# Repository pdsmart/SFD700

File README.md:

# SFD-700

Repository updated 08/11/2023

v1.0 - Functions in most machines, albeit, for an MZ-700 it requires MZ-700 memory mapping logic if used outside of an MZ-1U06 expansion box. Recommend only to view, not to build.

v1.1 - Functions but restrictions imposed with the GAL registers (ie. one clock all register) it couldnt satisfy my latest requirements, ie. MZ-700 memory mapping logic and Flash ROM paging. - Recommend only to view, not to build.

v1.2 - Hardware functions well on all machines tested (MZ-80A, MZ-700, MZ-1500, MZ-2000) and updates made to the Rom Filing System which basically works but has a few bugs I need to work out (fully functions as an FDC just the ROM based component of RFS has a bug and also I want to add FDC commands to the RFS Monitor). Also started updating CP/M and Basic (SA-5510, NASCOM Basic etc).

Documentation needs to be updated as it is out of date on my website, wip!

A Floppy Disk Interface card for the Sharp MZ series of machines (MZ-80B/MZ-80A/MZ-700/MZ-800/MZ-1500/MZ-2000/MZ-2200).

This project is based on an iconic floppy disk interface card from the 1980's by the Aachen based company, Kersten & Partner GmbH. The company produced two cards,
the SFD-700 for the Sharp MZ-700 and the SFD-800 for the Sharp MZ-800. 

Owning an original SFD-800, I reproduced the SFD-800 from the original schematic and the design can be seen here: https://eaw.app/sfd800/. This card has been well
tested and as the SFD-800 was quite a flexible design, it also worked in the MZ-80B/MZ-800/MZ-1500/MZ-2000/MZ-2200 computers. Unfortunately it didnt cater for the Sharp MZ-700 or indeed the Sharp MZ-80A.

To address the requirement of a floppy interface for the Sharp MZ-700 and MZ-80A, I considered reproducing the SFD-700 exactly but analysis showed it wouldnt work in an MZ-80A which uses a hardware trick to
address the CPU speed shortcomings. I thus decided, based on the SFD-800 schematics, to create a version 2 of the SFD-700 design which would work in all the Sharp MZ series computers.

Please see my website (in due course), https://eaw.app for more documentation and any recent updates.

If you want to build a v1.2 card, I have 6 boards spare I can ship, just pay me for the postage.

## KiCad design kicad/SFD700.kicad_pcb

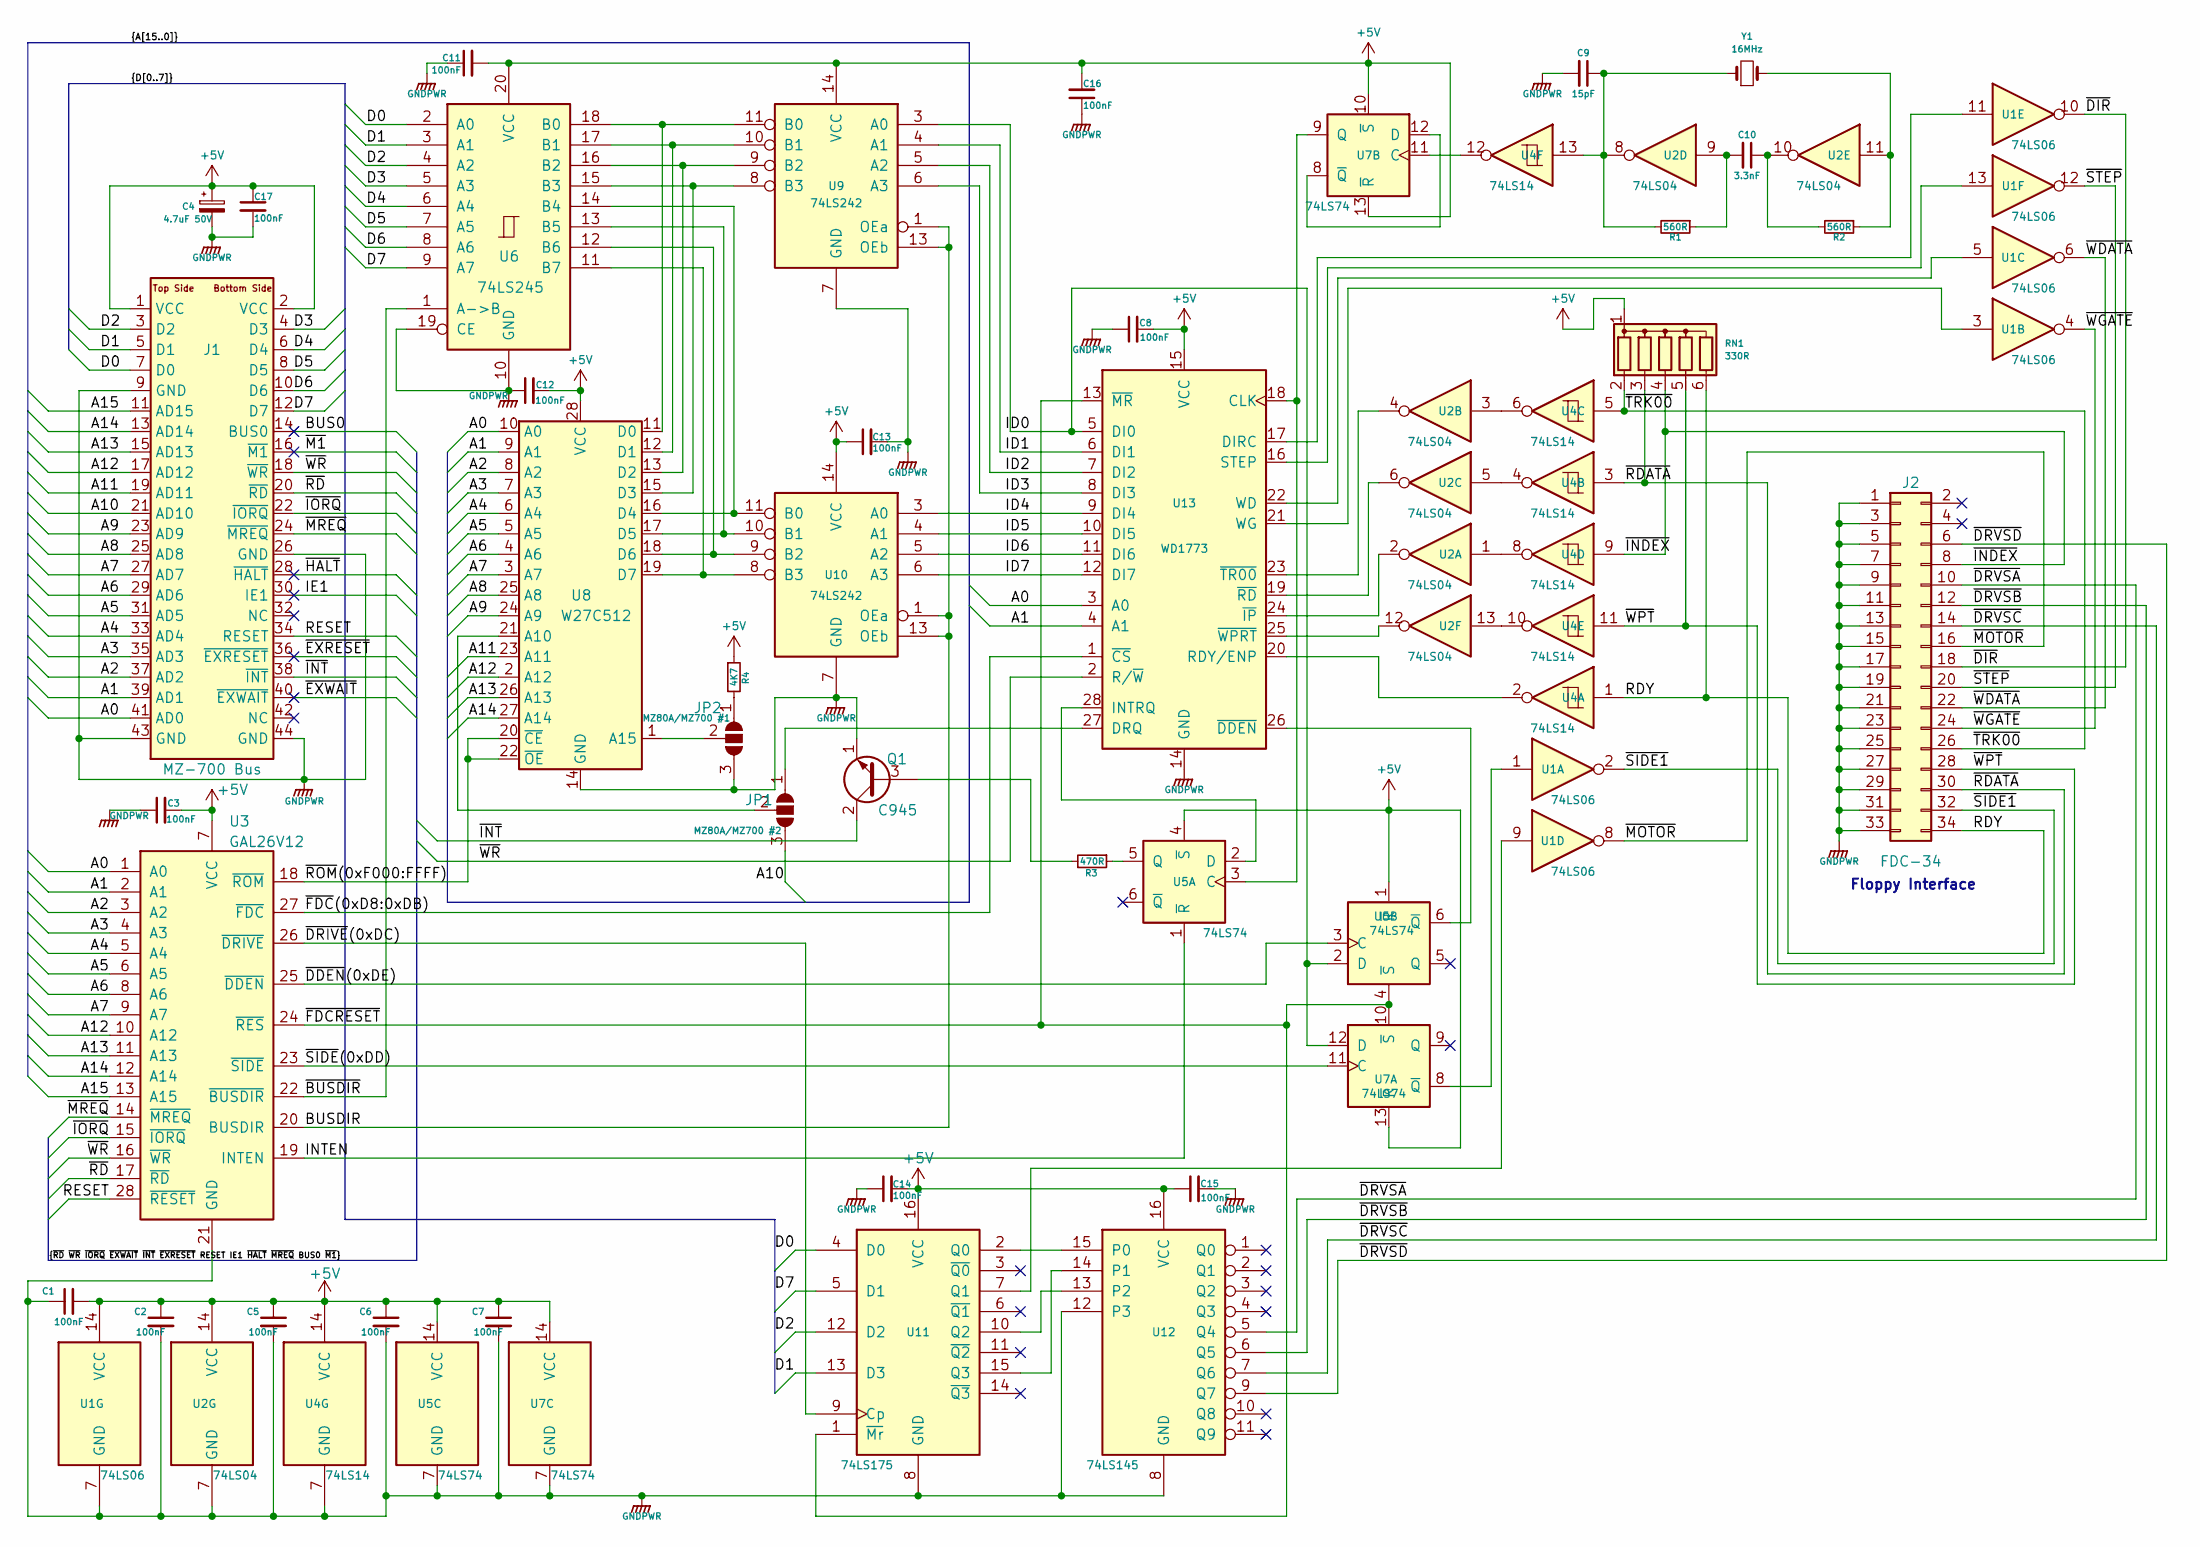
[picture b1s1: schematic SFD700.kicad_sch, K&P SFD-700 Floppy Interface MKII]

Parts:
C1, C2, C3, C5, C6, C7, C8, C11, C12, C13, C14, C15, C16, C17: 100nF; C_Disc_D5.0mm_W2.5mm_P2.50mm
C4: 4.7uF 50V; C_Radial_D6.3mm_H5.0mm_P2.50mm
C9: 15pF; C_Disc_D5.0mm_W2.5mm_P2.50mm
C10: 3.3nF; C_Disc_D5.0mm_W2.5mm_P2.50mm
J1: MZ-700 Bus; BUS_MZ800
J2: FDC-34; IDC-Header_2x17_P2.54mm_Horizontal_Lock_SFD700
JP1: MZ80A/MZ700 #2; PinHeader_1x03_P2.00mm_Vertical
JP2: MZ80A/MZ700 #1; PinHeader_1x03_P2.00mm_Vertical
Q1: C945; TO-92_Inline
R1, R2: 560R; R_Axial_DIN0204_L3.6mm_D1.6mm_P5.08mm_Horizontal
R3: 470R; R_Axial_DIN0204_L3.6mm_D1.6mm_P5.08mm_Horizontal
R4: 4K7; R_Axial_DIN0204_L3.6mm_D1.6mm_P5.08mm_Horizontal
RN1: 330R; R_Array_SIP6
U1: 74LS06; DIP-14_W7.62mm
U2: 74LS04; DIP-14_W7.62mm
U3: GAL26V12; PLCC-28_THT-Socket
U4: 74LS14; DIP-14_W7.62mm
U5, U7: 74LS74; DIP-14_W7.62mm
U6: 74LS245; DIP-20_W7.62mm
U8: W27C512; DIP-28_W15.24mm
U9, U10: 74LS242; DIP-14_W7.62mm
U11: 74LS175; DIP-16_W7.62mm
U12: 74LS145; DIP-16_W7.62mm
U13: WD1773; DIP-28_W15.24mm
Y1: 16MHz; Crystal_HC18-U_Vertical

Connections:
+5V: C1.2, C2.1, C3.2, C4.1, C5.1, C6.1, C7.1, C8.2, C11.2, C12.2, C13.1, C14.2, C15.1, C16.2, C17.1, J1.1 (VCC), J1.2 (VCC), R4.1, RN1.1 (common), U1.14 (VCC), U2.14 (VCC), U3.7 (VCC), U4.14 (VCC), U5.4 (~S), U5.13 (~R), U5.14 (VCC), U6.20 (VCC), U7.1 (~R), U7.10 (~S), U7.13 (~R), U7.14 (VCC), U8.28 (VCC), U9.14 (VCC), U10.14 (VCC), U11.16 (VCC), U12.16 (VCC), U13.15 (VCC)
/A0: J1.41 (AD0), U3.1 (A0), U8.10 (A0), U13.3 (A0)
/A1: J1.39 (AD1), U3.2 (A1), U8.9 (A1), U13.4 (A1)
/A2: J1.37 (AD2), U3.3 (A2), U8.8 (A2)
/A3: J1.35 (AD3), U3.4 (A3), U8.7 (A3)
/A4: J1.33 (AD4), U3.5 (A4), U8.6 (A4)
/A5: J1.31 (AD5), U3.6 (A5), U8.5 (A5)
/A6: J1.29 (AD6), U3.8 (A6), U8.4 (A6)
/A7: J1.27 (AD7), U3.9 (A7), U8.3 (A7)
/A8: J1.25 (AD8), U8.25 (A8)
/A9: J1.23 (AD9), U8.24 (A9)
/A10: J1.21 (AD10), JP1.3 (B)
/A11: J1.19 (AD11), U8.23 (A11)
/A12: J1.17 (AD12), U3.10 (A12), U8.2 (A12)
/A13: J1.15 (AD13), U3.11 (A13), U8.26 (A13)
/A14: J1.13 (AD14), U3.12 (A14), U8.27 (A14)
/A15: J1.11 (AD15), U3.13 (A15)
/BUS0: J1.14 (BUS0)
/BUSDIR: U3.20 (BUSDIR), U9.1 (OEa), U9.13 (OEb), U10.1 (OEa), U10.13 (OEb)
/D0: J1.7 (D0), U6.2 (A0), U11.4 (D0)
/D1: J1.5 (D1), U6.3 (A1), U11.13 (D3)
/D2: J1.3 (D2), U6.4 (A2), U11.12 (D2)
/D3: J1.4 (D3), U6.5 (A3)
/D4: J1.6 (D4), U6.6 (A4)
/D5: J1.8 (D5), U6.7 (A5)
/D6: J1.10 (D6), U6.8 (A6)
/D7: J1.12 (D7), U6.9 (A7), U11.5 (D1)
/ID0: U5.12 (D), U7.2 (D), U9.3 (A0), U13.5 (DI0)
/ID1: U9.4 (A1), U13.6 (DI1)
/ID2: U9.5 (A2), U13.7 (DI2)
/ID3: U9.6 (A3), U13.8 (DI3)
/ID4: U10.3 (A0), U13.9 (DI4)
/ID5: U10.4 (A1), U13.10 (DI5)
/ID6: U10.5 (A2), U13.11 (DI6)
/ID7: U10.6 (A3), U13.12 (DI7)
/IE1: J1.30 (IE1)
/INTEN: U3.19 (INTEN), U5.1 (~R)
/RDY: J2.34, RN1.6 (R5), U4.1
/RESET: J1.34 (RESET), U3.28 (~RESET)
/~BUSDIR: U3.22 (~BUSDIR), U6.1 (A->B)
/~DDEN(0xDE): U3.25 (~DDEN), U7.3 (C)
/~DIR: J2.18, U1.10
/~DRIVE(0xDC): U3.26 (~DRIVE), U11.9 (Cp)
/~DRVSA: J2.10, U12.5 (Q4)
/~DRVSB: J2.12, U12.6 (Q5)
/~DRVSC: J2.14, U12.7 (Q6)
/~DRVSD: J2.6, U12.9 (Q7)
/~EXRESET: J1.36 (~EXRESET)
/~EXWAIT: J1.40 (~EXWAIT)
/~FDCRESET: U3.24 (~RES), U5.10 (~S), U7.4 (~S), U11.1 (~Mr), U13.13 (~MR)
/~FDC(0xD8:0xDB): U3.27 (~FDC), U13.1 (~CS)
/~HALT: J1.28 (~HALT)
/~INDEX: J2.8, RN1.4 (R3), U4.9
/~INT: J1.38 (~INT), Q1.2 (C)
/~IORQ: J1.22 (~IORQ), U3.15 (~IORQ)
/~M1: J1.16 (~M1)
/~MOTOR: J2.16, U1.8
/~MREQ: J1.24 (~MREQ), U3.14 (~MREQ)
/~RDATA: J2.30, RN1.3 (R2), U4.3
/~RD: J1.20 (~RD), U3.17 (~RD)
/~ROM(0xF000:FFFF): U3.18 (~ROM), U8.20 (~CE), U8.22 (~OE)
/~SIDE1: J2.32, U1.2
/~SIDE(0xDD): U3.23 (~SIDE), U5.11 (C)
/~STEP: J2.20, U1.12
/~TRK00: J2.26, RN1.2 (R1), U4.5
/~WDATA: J2.22, U1.6
/~WGATE: J2.24, U1.4
/~WPT: J2.28, RN1.5 (R4), U4.11
/~WR: J1.18 (~WR), U3.16 (~WR), U13.2 (R/~W)
GNDPWR: C1.1, C2.2, C3.1, C4.2, C5.2, C6.2, C7.2, C8.1, C9.2, C11.1, C12.1, C13.2, C14.1, C15.2, C16.1, C17.2, J1.9 (GND), J1.26 (GND), J1.43 (GND), J1.44 (GND), J2.1, J2.3, J2.5, J2.7, J2.9, J2.11, J2.13, J2.15, J2.17, J2.19, J2.21, J2.23, J2.25, J2.27, J2.29, J2.31, J2.33, JP2.3 (B), Q1.1 (E), U1.7 (GND), U2.7 (GND), U3.21 (GND), U4.7 (GND), U5.7 (GND), U6.10 (GND), U6.19 (CE), U7.7 (GND), U8.14 (GND), U9.7 (GND), U10.7 (GND), U11.8 (GND), U12.8 (GND), U12.12 (P3), U13.14 (GND)
unnamed: C9.1, R1.2, U2.8, U4.13, Y1.1
unnamed: C10.1, R2.2, U2.10
unnamed: C10.2, R1.1, U2.9
unnamed: JP1.1 (A), U13.27 (DRQ)
unnamed: JP1.2 (C), U8.21 (A10)
unnamed: JP2.1 (A), R4.2
unnamed: JP2.2 (C), U8.1 (A15)
unnamed: Q1.3 (B), R3.2
unnamed: R2.1, U2.11, Y1.2
unnamed: U2.1, U4.8
unnamed: U2.3, U4.6
unnamed: U2.5, U4.4
unnamed: U2.13, U4.10
unnamed: R3.1, U5.5 (Q)
unnamed: U1.1, U5.8 (~Q)
unnamed: U6.18 (B0), U8.11 (D0), U9.11 (B0)
unnamed: U6.17 (B1), U8.12 (D1), U9.10 (B1)
unnamed: U6.16 (B2), U8.13 (D2), U9.9 (B2)
unnamed: U6.15 (B3), U8.15 (D3), U9.8 (B3)
unnamed: U4.12, U7.11 (C)
unnamed: U7.8 (~Q), U7.12 (D)
unnamed: U6.14 (B4), U8.16 (D4), U10.11 (B0)
unnamed: U6.13 (B5), U8.17 (D5), U10.10 (B1)
unnamed: U6.12 (B6), U8.18 (D6), U10.9 (B2)
unnamed: U6.11 (B7), U8.19 (D7), U10.8 (B3)
unnamed: U11.2 (Q0), U12.15 (P0)
unnamed: U1.9, U11.7 (Q1)
unnamed: U11.10 (Q2), U12.13 (P2)
unnamed: U11.15 (Q3), U12.14 (P1)
unnamed: U5.3 (C), U7.9 (Q), U13.18 (CLK)
unnamed: U1.11, U13.17 (DIRC)
unnamed: U5.2 (D), U13.28 (INTRQ)
unnamed: U4.2, U13.20 (RDY/ENP)
unnamed: U1.13, U13.16 (STEP)
unnamed: U1.5, U13.22 (WD)
unnamed: U1.3, U13.21 (WG)
unnamed: U7.6 (~Q), U13.26 (~DDEN)
unnamed: U2.2, U13.24 (~IP)
unnamed: U2.6, U13.19 (~RD)
unnamed: U2.4, U13.23 (~TR00)
unnamed: U2.12, U13.25 (~WPRT)

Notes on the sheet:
Floppy Interface

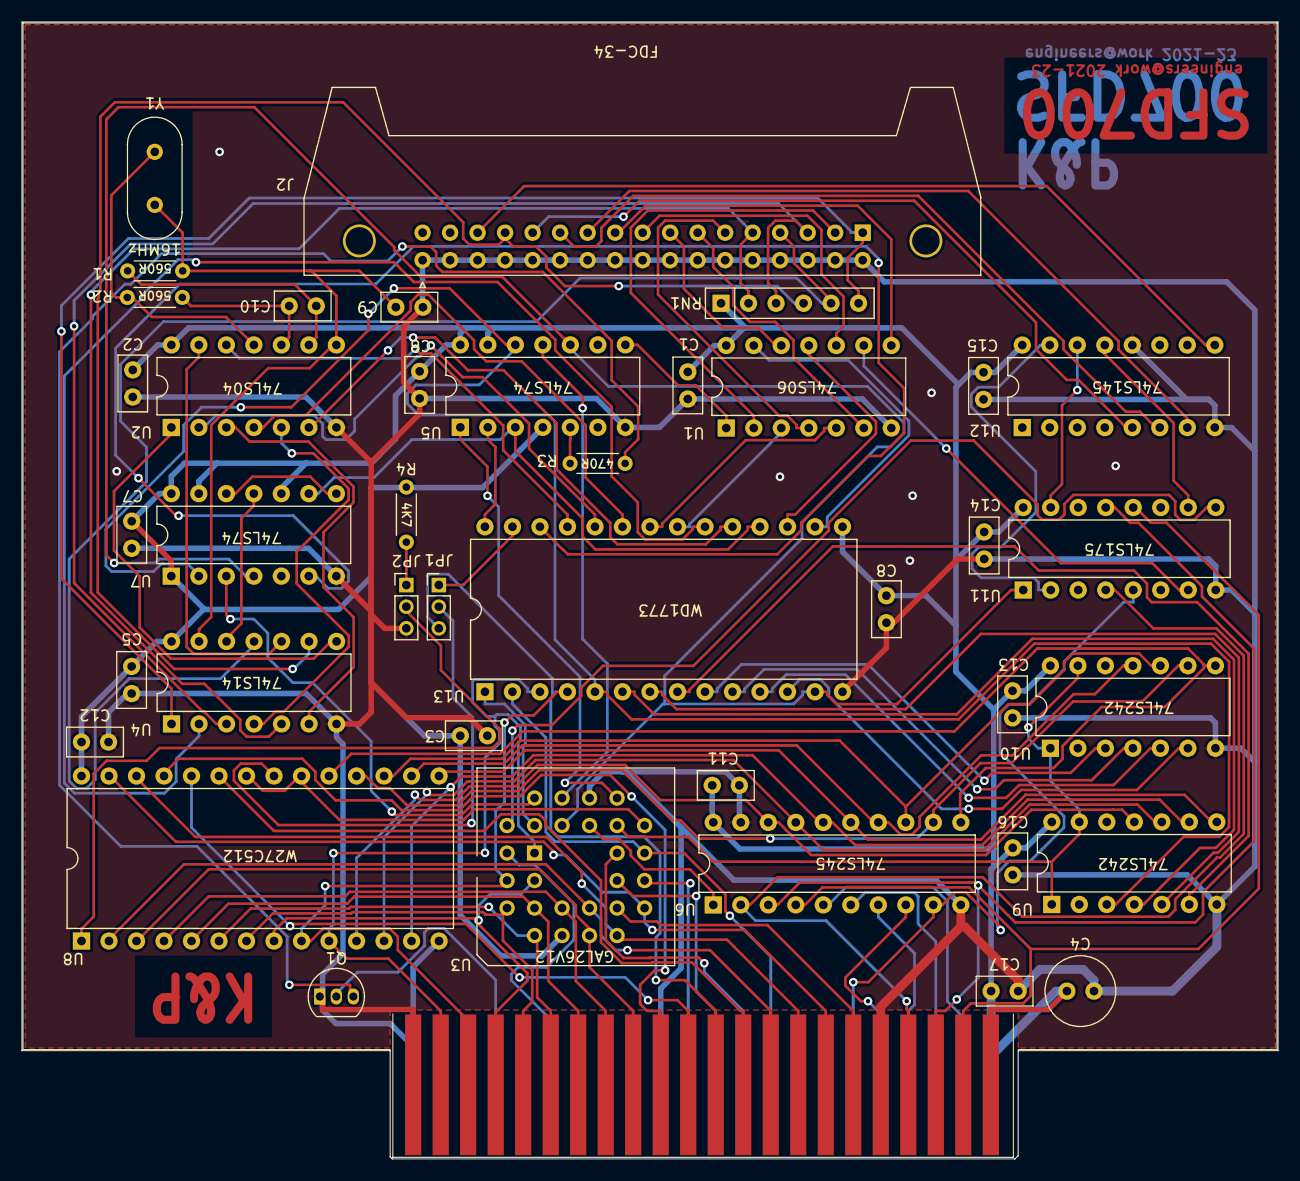
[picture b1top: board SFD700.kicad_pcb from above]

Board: 2 copper layers, 116.0 x 105.0 mm, 41 parts (0 on the bottom side), 105 nets.

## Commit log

2023-04-18 Repo setup
2023-04-18 First release
2023-05-10 Updates for GAL logic
2023-07-23 Updates to GAL PLD code
2023-11-06 Update README.md
    Update on suitability for use.
2023-11-06 Update README.md
    Added link to v1.2
2023-11-08 Updates since v1.0
2023-11-08 Updates from v1.0
2025-09-01 Added GAL compiled files
